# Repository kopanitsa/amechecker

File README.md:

# amechecker

Please refer　http://qiita.com/kopanitsa/items/08a26271a0845214502b

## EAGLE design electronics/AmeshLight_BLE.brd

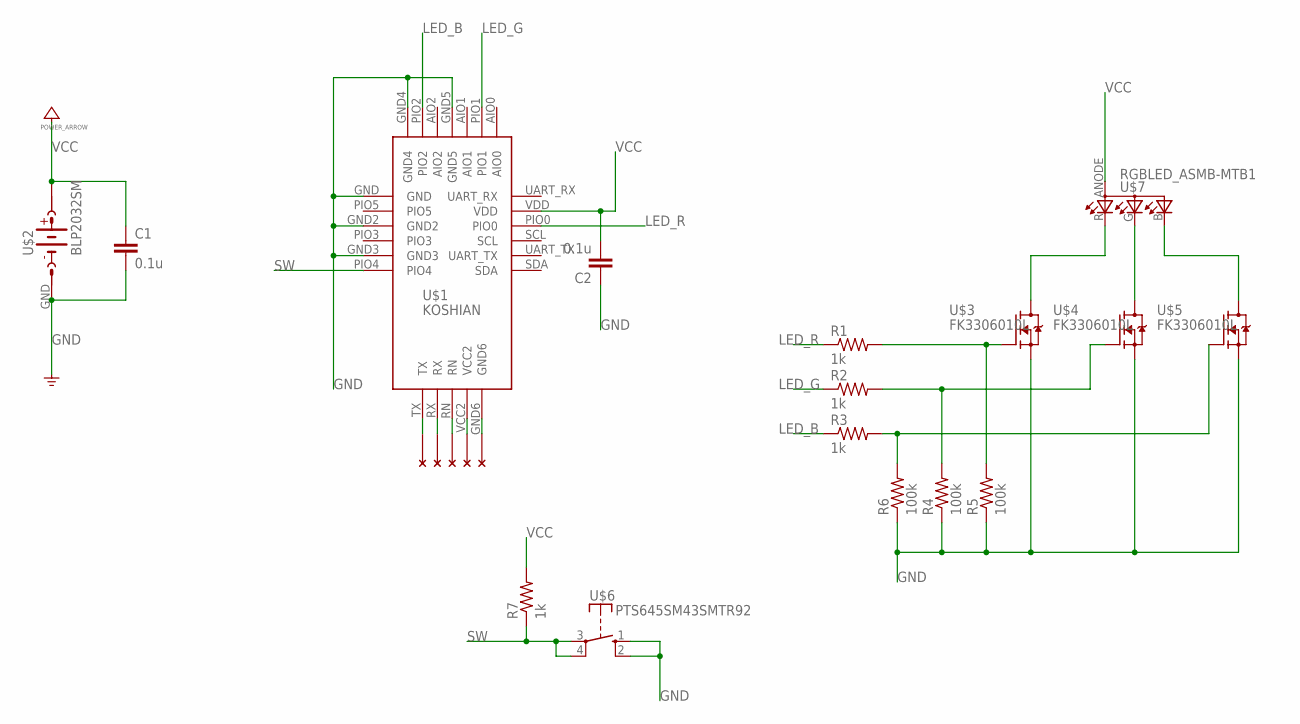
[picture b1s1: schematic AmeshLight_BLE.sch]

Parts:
C1, C2: 0.1u; C0603
R1, R2, R3, R7: 1k; R0603
R4, R5, R6: 100k; R0603
U$1: KOSHIAN
U$2: BLP2032SM
U$3, U$4, U$5: FK3306010L
U$6: PTS645SM43SMTR92
U$7: RGBLED_ASMB-MTB1

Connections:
GND: C1.2, C2.1, R4.1, R5.1, R6.1, U$1.GND, U$1.GND2, U$1.GND3, U$1.GND4, U$1.GND5, U$2.GND, U$3.S, U$4.S, U$5.S, U$6.1 (S), U$6.2
LED_B: R3.1, U$1.PIO2
LED_G: R2.1, U$1.PIO1
LED_R: R1.1, U$1.PIO0
unnamed: U$3.D, U$7.R (1RED)
unnamed: U$4.D, U$7.G (2GREEN)
unnamed: U$5.D, U$7.B (3BLUE)
unnamed: R3.2, R6.2, U$5.G
unnamed: R1.2, R5.2, U$3.G
unnamed: R2.2, R4.2, U$4.G
SW: R7.1, U$1.PIO4, U$6.3, U$6.4
VCC: C1.1, C2.2, R7.2, U$1.VDD, U$2.VCC, U$7.ANODE (4)

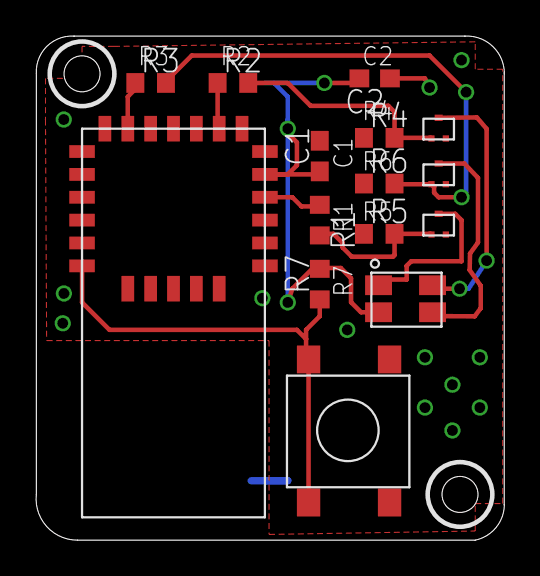
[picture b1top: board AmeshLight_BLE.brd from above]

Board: 2 copper layers, 26.0 x 28.0 mm, 16 parts (1 on the bottom side), 12 nets.
